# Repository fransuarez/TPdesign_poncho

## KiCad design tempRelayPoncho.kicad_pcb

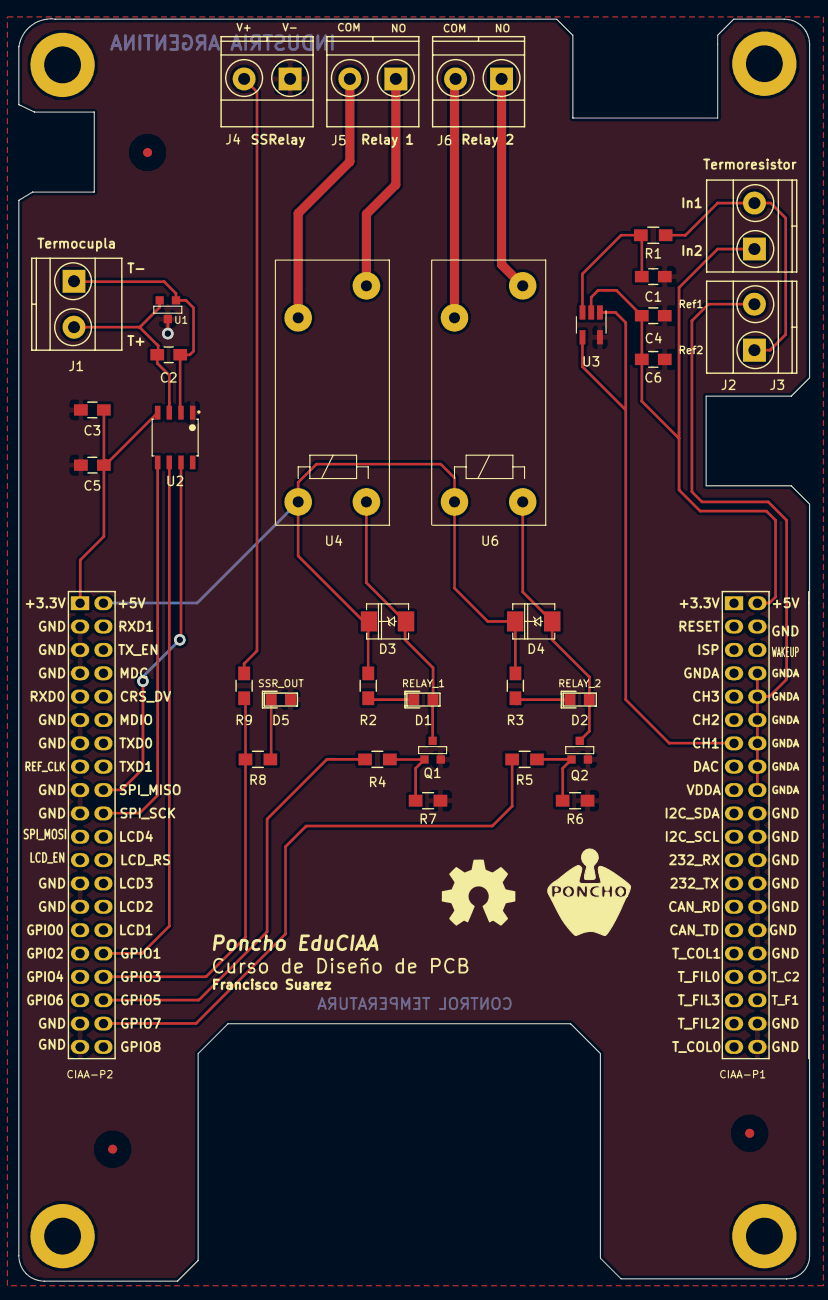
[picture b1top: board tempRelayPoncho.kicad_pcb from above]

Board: 2 copper layers, 86.0 x 137.3 mm, 38 parts (0 on the bottom side), 28 nets.

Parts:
C1, C3, C4: 10u; C_0805_HandSoldering
C2, C5, C6: 100n; C_0805_HandSoldering
D1: RELAY_1; LED-0805
D2: RELAY_2; LED-0805
D3, D4: MRA4003T3G; DO-214AA(SMB)
D5: SSR_OUT; LED-0805
F1, F2, F3: FIDUCIAL; Fiducial_1mm
G101: Logo_OSHWA
J1, J2, J3, J4, J5, J6: Screw_Terminal_1x02; TerminalBlock_Pheonix_MKDS1.5-2pol
Q1, Q2: MMBT3904; SOT23_NPN
R1, R6, R7: 10k; R_0805_HandSoldering
R2, R3, R4, R5, R8: 1k; R_0805_HandSoldering
R9: 100; R_0805_HandSoldering
U1: NUP2105LT1G; SOT23_NPN
U2: MAX31855KASA+; SOIC-8
U3: MCP601R; SOT-23-5_HandSoldering
U4, U6: G5LE-1A-5DC; Relay_G5LE-1A-5DC-5mm
XA1: Conn_Poncho2P_2x_20x2; Conn_Poncho_Completo

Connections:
+3V3: C3.2, C5.2, U2.4, XA1.41
+5V: C4.2, C6.2, J2.1, U3.2, XA1.2
+5VD: D3.2, D4.2, R2.2, R3.2, U4.5, U6.5, XA1.42
/conector_ciaa/ADC_1: U3.1, U3.4, XA1.13
/conector_ciaa/GPIO_1: U2.6, XA1.72
/conector_ciaa/GPIO_3: R8.2, R9.2, XA1.74
/conector_ciaa/GPIO_5: R4.2, XA1.76
/conector_ciaa/GPIO_7: R5.2, XA1.78
/inputs_temp/MISO_TCUP: U2.7, XA1.58
/inputs_temp/SCK_TCUP: U2.5, XA1.60
GND: C1.1, C3.1, C4.1, C5.1, C6.1, D5.1, J4.1, Q1.2, Q2.2, R6.1, R7.1, U1.3, U2.1, U3.5, XA1.4, XA1.20, XA1.22, XA1.24, XA1.26, XA1.28, XA1.30, XA1.32, XA1.38, XA1.40, XA1.43, XA1.45, XA1.47, XA1.51, XA1.53, XA1.57, XA1.59, XA1.65, XA1.67, XA1.77, XA1.79
GNDA: J3.2, XA1.8, XA1.10, XA1.12, XA1.14, XA1.16, XA1.18
unnamed: C1.2, R1.1, U3.3
unnamed: C2.1, J1.2, U1.2, U2.3
unnamed: C2.2, J1.1, U1.1, U2.2
unnamed: D1.1, D3.1, Q1.3, U4.1
unnamed: D1.2, R2.1
unnamed: D2.1, D4.1, Q2.3, U6.1
unnamed: D2.2, R3.1
unnamed: D5.2, R8.1
unnamed: J2.2, J3.1, R1.2
unnamed: J4.2, R9.1
unnamed: J5.1, U4.3
unnamed: J5.2, U4.4
unnamed: J6.1, U6.3
unnamed: J6.2, U6.4
unnamed: Q1.1, R4.1, R7.2
unnamed: Q2.1, R5.1, R6.2

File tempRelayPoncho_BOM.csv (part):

Source:,/home/fran/CIAA/Repositorios/TPpcbdesign/tempRelayPoncho.sch
Date:,Sun 16 Jul 2017 10:07:31 PM ART
Tool:,Eeschema 4.0.6-e0-6349~53~ubuntu16.04.1
Generator:,/home/fran/Documents/Diseño de circuitos impresos/TPs/practica2/tools/bom_csv_grouped_by_value.py
Component Count:,37

Individual Components:

Item,Qty,Reference(s),Value,LibPart,Footprint,Datasheet,Descripcion,Description,Digikey#,Manf,Manf#,Mouser#
,,C1,10u,TempRelay:C,footprints:C_0805_HandSoldering,c02e-2905.pdf,,Multilayer Ceramic Capacitors MLCC - SMD/SMT 0805 10uF 6.3volts X5R 20%,490-1718-1-ND,Murata,GRM21BR60J106ME19L,81-GRM21BR60J106ME19
,,C2,100n,TempRelay:C,footprints:C_0805_HandSoldering,c02e-2905.pdf,,Multilayer Ceramic Capacitors MLCC - SMD/SMT 0.1uF 10Volts U2J 5%,490-11592-1-ND,Murata,GRM21B7U1A104JA01L,81-GRM21B7U1A104JA1L
,,C3,10u,TempRelay:C,footprints:C_0805_HandSoldering,c02e-2905.pdf,,Multilayer Ceramic Capacitors MLCC - SMD/SMT 0805 10uF 6.3volts X5R 20%,490-1718-1-ND,Murata,GRM21BR60J106ME19L,81-GRM21BR60J106ME19
,,C4,10u,TempRelay:C,footprints:C_0805_HandSoldering,c02e-2905.pdf,,Multilayer Ceramic Capacitors MLCC - SMD/SMT 0805 10uF 6.3volts X5R 20%,490-1718-1-ND,Murata,GRM21BR60J106ME19L,81-GRM21BR60J106ME19
,,C5,100n,TempRelay:C,footprints:C_0805_HandSoldering,c02e-2905.pdf,,Multilayer Ceramic Capacitors MLCC - SMD/SMT 0.1uF 10Volts U2J 5%,490-11592-1-ND,Murata,GRM21B7U1A104JA01L,81-GRM21B7U1A104JA1L
,,C6,100n,TempRelay:C,footprints:C_0805_HandSoldering,c02e-2905.pdf,,Multilayer Ceramic Capacitors MLCC - SMD/SMT 0.1uF 10Volts U2J 5%,490-11592-1-ND,Murata,GRM21B7U1A104JA01L,81-GRM21B7U1A104JA1L
,,D1,LED_ALT,TempRelay:LED_ALT,footprints:LED-0805,qtlp630c-2.pdf,,Red 645nm LED Indication - Discrete 1.9V 0805 (2012 Metric),1080-1412-2-ND,Everlight Electronics Co Ltd,QTLP630C7TR,Value
,,D2,LED_ALT,TempRelay:LED_ALT,footprints:LED-0805,qtlp630c-2.pdf,,Red 645nm LED Indication - Discrete 1.9V 0805 (2012 Metric),1080-1412-2-ND,Everlight Electronics Co Ltd,QTLP630C7TR,Value
,,D3,MRA4003T3G,TempRelay:DIODE,footprints:DO-214AA(SMB),MRA4003T3-D.PDF,,Diode Standard 300V 1A SMA,MRA4003T3GOSTR-ND,ON Semiconductor,MRA4003T3G,Value
,,D4,MRA4003T3G,TempRelay:DIODE,footprints:DO-214AA(SMB),MRA4003T3-D.PDF,,Diode Standard 300V 1A SMA,MRA4003T3GOSTR-ND,ON Semiconductor,MRA4003T3G,Value
,,D5,LED_ALT,TempRelay:LED_ALT,footprints:LED-0805,qtlp630c-2.pdf,,Red 645nm LED Indication - Discrete 1.9V 0805 (2012 Metric),1080-1412-2-ND,Everlight Electronics Co Ltd,QTLP630C7TR,Value
,,F1,FIDUCIAL,TempRelay:FIDUCIAL,footprints:Fiducial_1mm,,FIDUCIAL,,,,,
,,F2,FIDUCIAL,TempRelay:FIDUCIAL,footprints:Fiducial_1mm,,FIDUCIAL,,,,,
,,F3,FIDUCIAL,TempRelay:FIDUCIAL,footprints:Fiducial_1mm,,FIDUCIAL,,,,,
,,J1,Screw_Terminal_1x02,TempRelay:Screw_Terminal_1x02,footprints:TerminalBlock_Pheonix_MKDS1.5-2pol,MKDS Phoenix 1-5.pdf,,2 Position Wire to Board Terminal Block Horizontal with Board 0.138,277-5719-ND,Phoenix Contact,1751248,Value
,,J2,Screw_Terminal_1x02,TempRelay:Screw_Terminal_1x02,footprints:TerminalBlock_Pheonix_MKDS1.5-2pol,MKDS Phoenix 1-5.pdf,,2 Position Wire to Board Terminal Block Horizontal with Board 0.138,277-5719-ND,Phoenix Contact,1751248,Value
,,J3,Screw_Terminal_1x02,TempRelay:Screw_Terminal_1x02,footprints:TerminalBlock_Pheonix_MKDS1.5-2pol,MKDS Phoenix 1-5.pdf,,2 Position Wire to Board Terminal Block Horizontal with Board 0.138,277-5719-ND,Phoenix Contact,1751248,Value
,,J4,Screw_Terminal_1x02,TempRelay:Screw_Terminal_1x02,footprints:TerminalBlock_Pheonix_MKDS1.5-2pol,MKDS Phoenix 1-5.pdf,,"2 Position Wire to Board Terminal Block Horizontal with Board 0.138"" (3.50mm) Through Hole",277-5719-ND,Phoenix Contact,1751248,Value
,,J5,Screw_Terminal_1x02,TempRelay:Screw_Terminal_1x02,footprints:TerminalBlock_Pheonix_MKDS1.5-2pol,MKDS Phoenix 1-5.pdf,,"2 Position Wire to Board Terminal Block Horizontal with Board 0.138"" (3.50mm) Through Hole",277-5719-ND,Phoenix Contact,1751248,Value
,,J6,Screw_Terminal_1x02,TempRelay:Screw_Terminal_1x02,footprints:TerminalBlock_Pheonix_MKDS1.5-2pol,MKDS Phoenix 1-5.pdf,,"2 Position Wire to Board Terminal Block Horizontal with Board 0.138"" (3.50mm) Through Hole",277-5719-ND,Phoenix Contact,1751248,Value
,,Q1,MMBT3904,TempRelay:MMBT3904,footprints:SOT23_NPN,2N3904-82270.pdf,,Bipolar (BJT) Transistor NPN 40V 200mA 300MHz 350mW,MMBT3904FSCT-ND,ON Semiconductor,MMBT3904,Value
,,Q2,MMBT3904,TempRelay:MMBT3904,footprints:SOT23_NPN,2N3904-82270.pdf,,Bipolar (BJT) Transistor NPN 40V 200mA 300MHz 350mW,MMBT3904FSCT-ND,ON Semiconductor,MMBT3904,Value
,,R1,10k,TempRelay:R,footprints:R_0805_HandSoldering,Yageo_08112016_RC0805-968729.pdf,,Thick Film Resistors - SMD 10K OHM 1%,311-10.0KCRCT-ND,Yageo,RC0805FR-0710KL,603-RC0805FR-0710KL
,,R2,1k,TempRelay:R,footprints:R_0805_HandSoldering,../Datasheets/Yageo_08112016_RC0805-968729.pdf,,Thick Film Resistors - SMD 1K OHM 1%,311-1.00KCRCT-ND,Yageo,RC0805FR-071KL,603-RC0805FR-071KL
,,R3,1k,TempRelay:R,footprints:R_0805_HandSoldering,../Datasheets/Yageo_08112016_RC0805-968729.pdf,,Thick Film Resistors - SMD 1K OHM 1%,311-1.00KCRCT-ND,Yageo,RC0805FR-071KL,603-RC0805FR-071KL
,,R4,1k,TempRelay:R,footprints:R_0805_HandSoldering,../Datasheets/Yageo_08112016_RC0805-968729.pdf,,Thick Film Resistors - SMD 1K OHM 1%,311-1.00KCRCT-ND,Yageo,RC0805FR-071KL,603-RC0805FR-071KL
,,R5,1k,TempRelay:R,footprints:R_0805_HandSoldering,../Datasheets/Yageo_08112016_RC0805-968729.pdf,,Thick Film Resistors - SMD 1K OHM 1%,311-1.00KCRCT-ND,Yageo,RC0805FR-071KL,603-RC0805FR-071KL
,,R6,10k,TempRelay:R,footprints:R_0805_HandSoldering,../Datasheets/Yageo_08112016_RC0805-968729.pdf,,Thick Film Resistors - SMD 10K OHM 1%,311-10.0KCRCT-ND,Yageo,RC0805FR-0710KL,603-RC0805FR-0710KL
,,R7,10k,TempRelay:R,footprints:R_0805_HandSoldering,../Datasheets/Yageo_08112016_RC0805-968729.pdf,,Thick Film Resistors - SMD 10K OHM 1%,311-10.0KCRCT-ND,Yageo,RC0805FR-0710KL,603-RC0805FR-0710KL
,,R8,1k,TempRelay:R,footprints:R_0805_HandSoldering,../Datasheets/Yageo_08112016_RC0805-968729.pdf,,Thick Film Resistors - SMD 1K OHM 1%,311-1.00KCRCT-ND,Yageo,RC0805FR-071KL,603-RC0805FR-071KL
,,R9,100,TempRelay:R,footprints:R_0805_HandSoldering,../Datasheets/Yageo_08112016_RC0805-968729.pdf,,1Thick Film Resistors - SMD 100 OHM 1%,311-100CRCT-ND,Yageo,RC0805FR-07100RL,603-RC0805FR-07100RL
,,U1,NUP2105LT1G,TempRelay:NUP2105LT1G,footprints:SC-59_Handsoldering,NUP2105L-D-771105.pdf,,TVS DIODE 24VWM 44VC,NUP2105LT1GOSCT-ND,ON Semiconductor,NUP2105LT1G,Value
,,U2,MAX31855KASA+,TempRelay:MAX31855KASA+,footprints:SOIC-8,MAX31855.pdf,,Sensor Interface Thermocouple To Digital Converter,MAX31855KASA+-ND,Maxim Integrated,MAX31855KASA+,Value
,,U3,MCP601R,TempRelay:MCP601R,footprints:SOT-23-5_HandSoldering,"MCP601,2,3,4.pdf",,Operational Amplifiers - Op Amps Single 2.7V,Value,Microchip Technology,MCP601T-I/OT,579-MCP601T-I/OT
,,U4,G5LE-1A-5DC,TempRelay:G5LE-1A-5DC,footprints:Relay_G5LE-1A-5DC-5mm,,,,,,,
,,U6,G5LE-1A-5DC,TempRelay:G5LE-1A-5DC,footprints:Relay_G5LE-1A-5DC-5mm,,,,,,,
,,XA1,Conn_Poncho2P_2x_20x2,TempRelay:Conn_Poncho2P_2x_20x2,footprints:Conn_Poncho_Completo,,,Value,Value,Value,Value,Value



Collated Components:

Item,Qty,Reference(s),Value,LibPart,Footprint,Datasheet,Descripcion,Description,Digikey#,Manf,Manf#,Mouser#
1,3,"C1, C3, C4",10u,TempRelay:C,footprints:C_0805_HandSoldering,c02e-2905.pdf,,Multilayer Ceramic Capacitors MLCC - SMD/SMT 0805 10uF 6.3volts X5R 20%,490-1718-1-ND,Murata,GRM21BR60J106ME19L,81-GRM21BR60J106ME19
2,3,"C2, C5, C6",100n,TempRelay:C,footprints:C_0805_HandSoldering,c02e-2905.pdf,,Multilayer Ceramic Capacitors MLCC - SMD/SMT 0.1uF 10Volts U2J 5%,490-11592-1-ND,Murata,GRM21B7U1A104JA01L,81-GRM21B7U1A104JA1L
3,3,"D1, D2, D5",LED_ALT,TempRelay:LED_ALT,footprints:LED-0805,qtlp630c-2.pdf,,Red 645nm LED Indication - Discrete 1.9V 0805 (2012 Metric),1080-1412-2-ND,Everlight Electronics Co Ltd,QTLP630C7TR,Value
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
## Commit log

2017-05-30 Inicio de repositorio
2017-06-22 Primeros pasos
    Agrego primeros esquematicos y datasheets.
2017-06-25 Primer version
    Esquematico completo, faltan notas del revisor.
2017-06-26 Primer revision
    Se agregar correcciones del revisor. Se modifica entrada termocupla.
2017-07-04 Correciones y ubicacion en pcb
    Se corrige problema con archivo inputs_temp.sch
    Se corrige problema con footprints de Realys y transistores U4 y U6
    Se hace primera ubicacion tentativa en PCB de componentes.
2017-07-16 Primer version del PCB
    Se agregan modificaciones segun primer correccion. Se carga primer version del PCB.
2017-07-17 Correcciones de Revisor
    Se agregan algunas de las correcciones del revisor. Las que restan se implementaran luego.
2017-08-09 Correccion Final
    Se trabajo sobre correcciones de 2da revision. Se agregaron archivos gerbers, BOM, y objetos 3D
2017-08-09 Pines al 3D
    Se agregan tiras de pines y capturas del modelo en la carpeta docs
